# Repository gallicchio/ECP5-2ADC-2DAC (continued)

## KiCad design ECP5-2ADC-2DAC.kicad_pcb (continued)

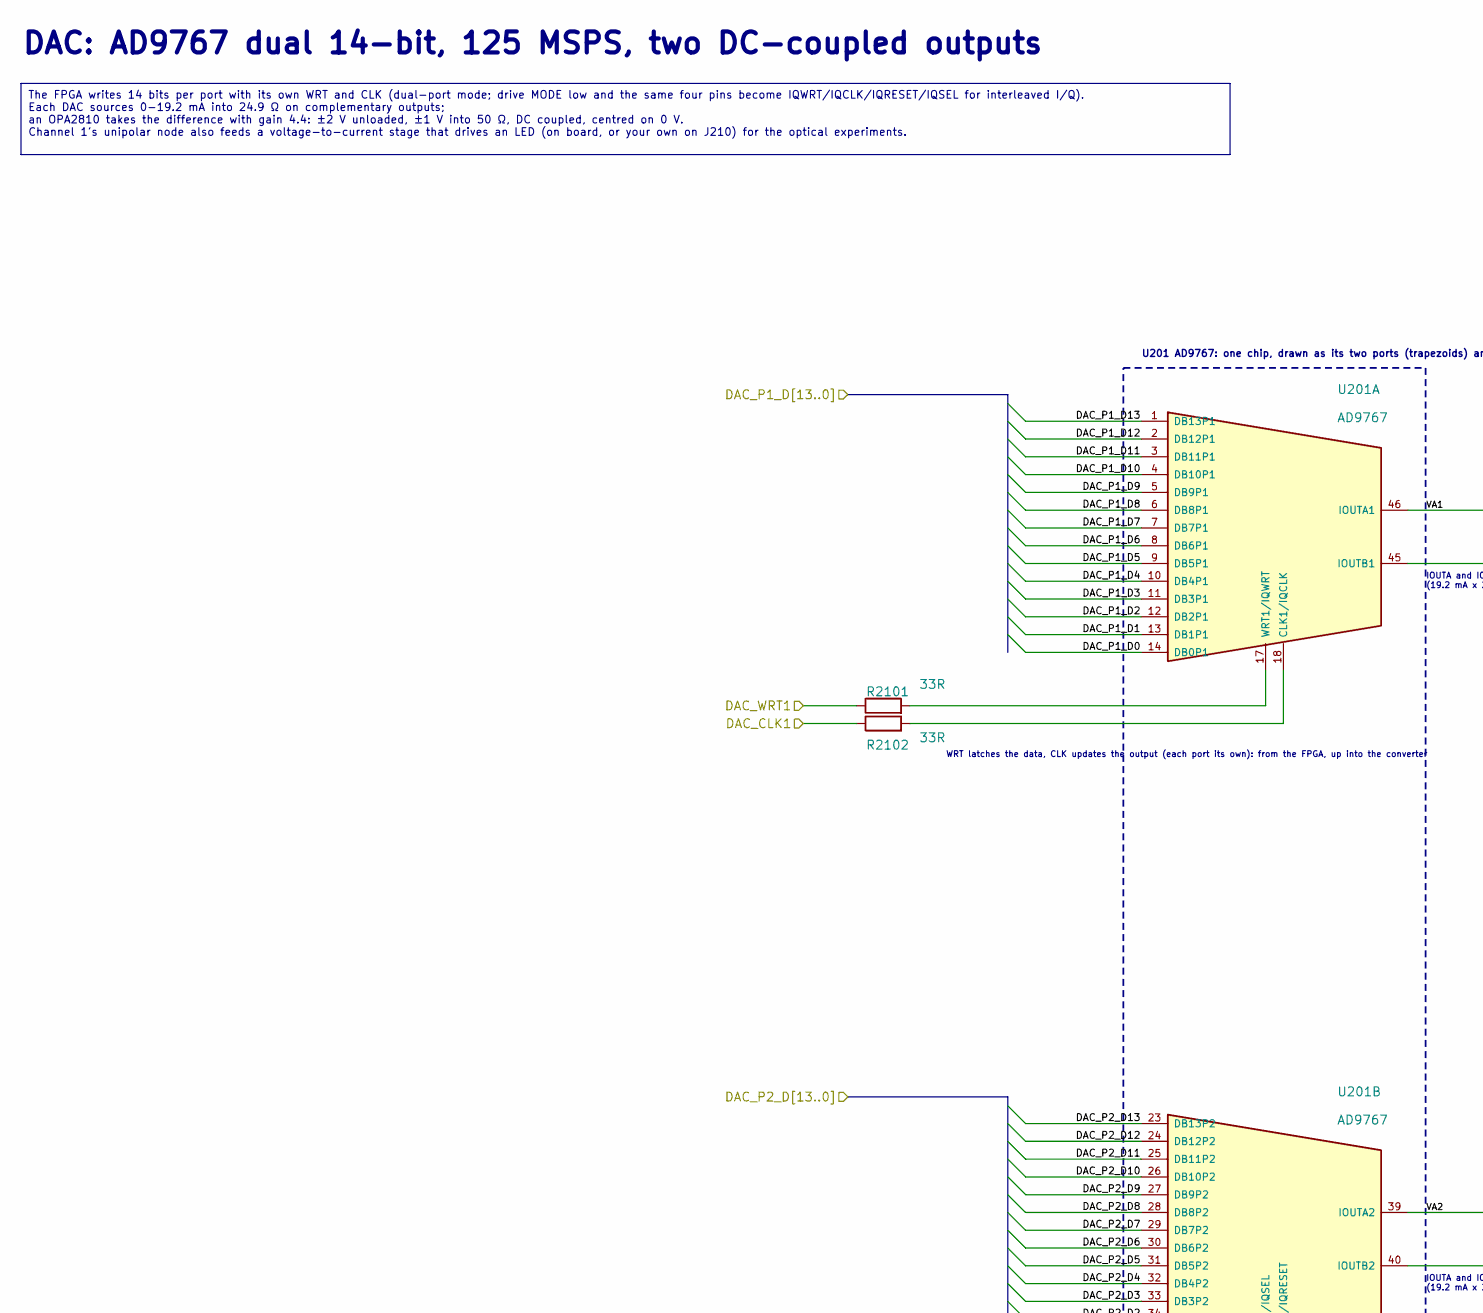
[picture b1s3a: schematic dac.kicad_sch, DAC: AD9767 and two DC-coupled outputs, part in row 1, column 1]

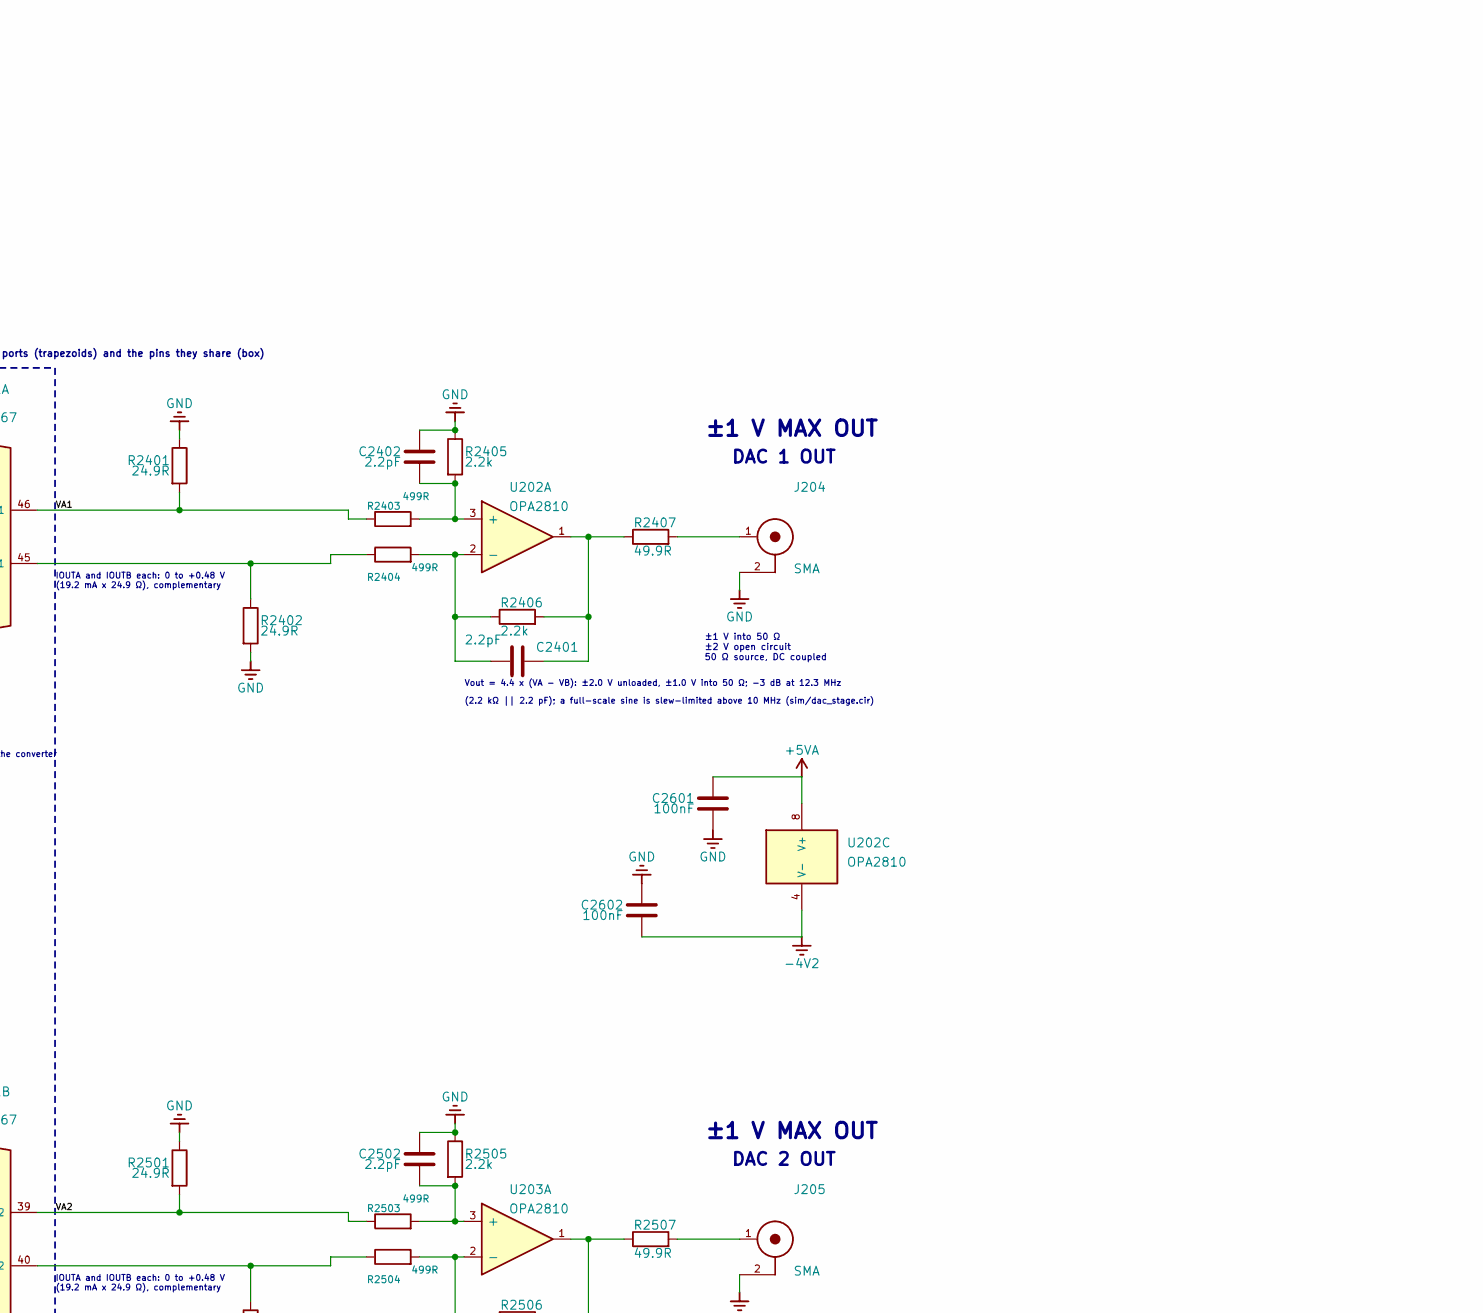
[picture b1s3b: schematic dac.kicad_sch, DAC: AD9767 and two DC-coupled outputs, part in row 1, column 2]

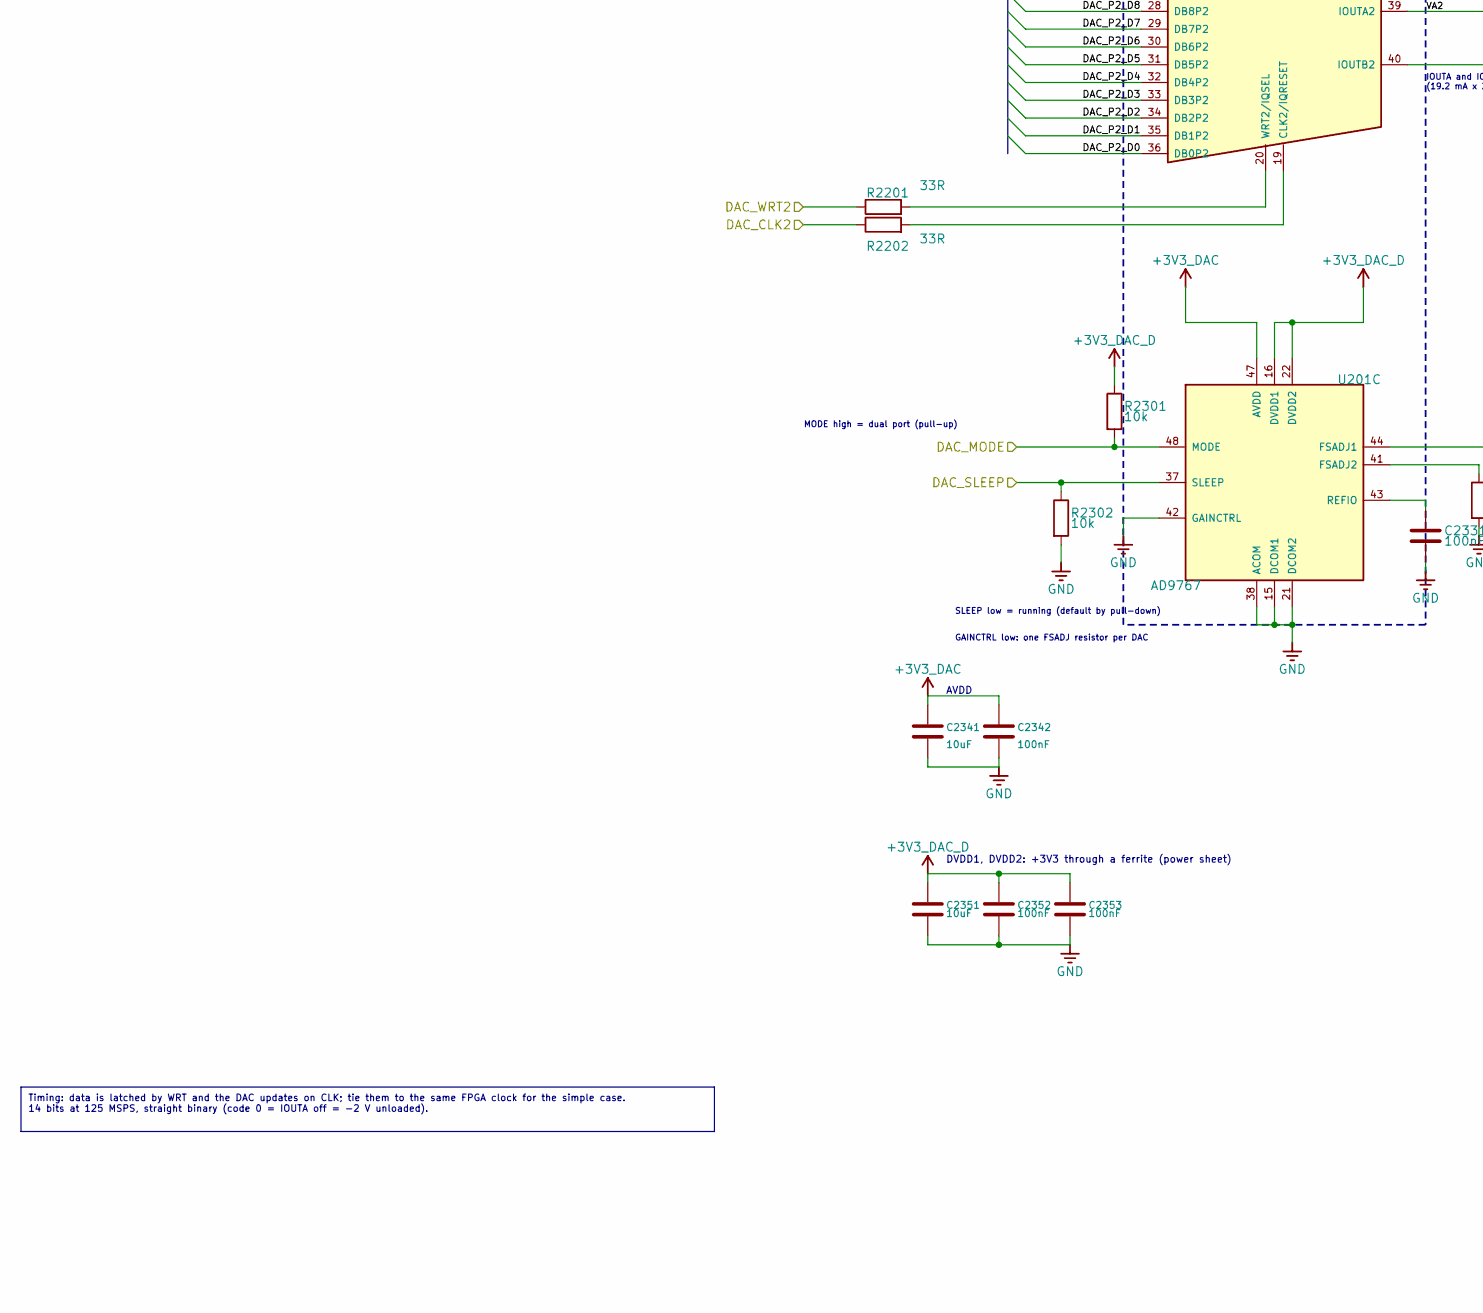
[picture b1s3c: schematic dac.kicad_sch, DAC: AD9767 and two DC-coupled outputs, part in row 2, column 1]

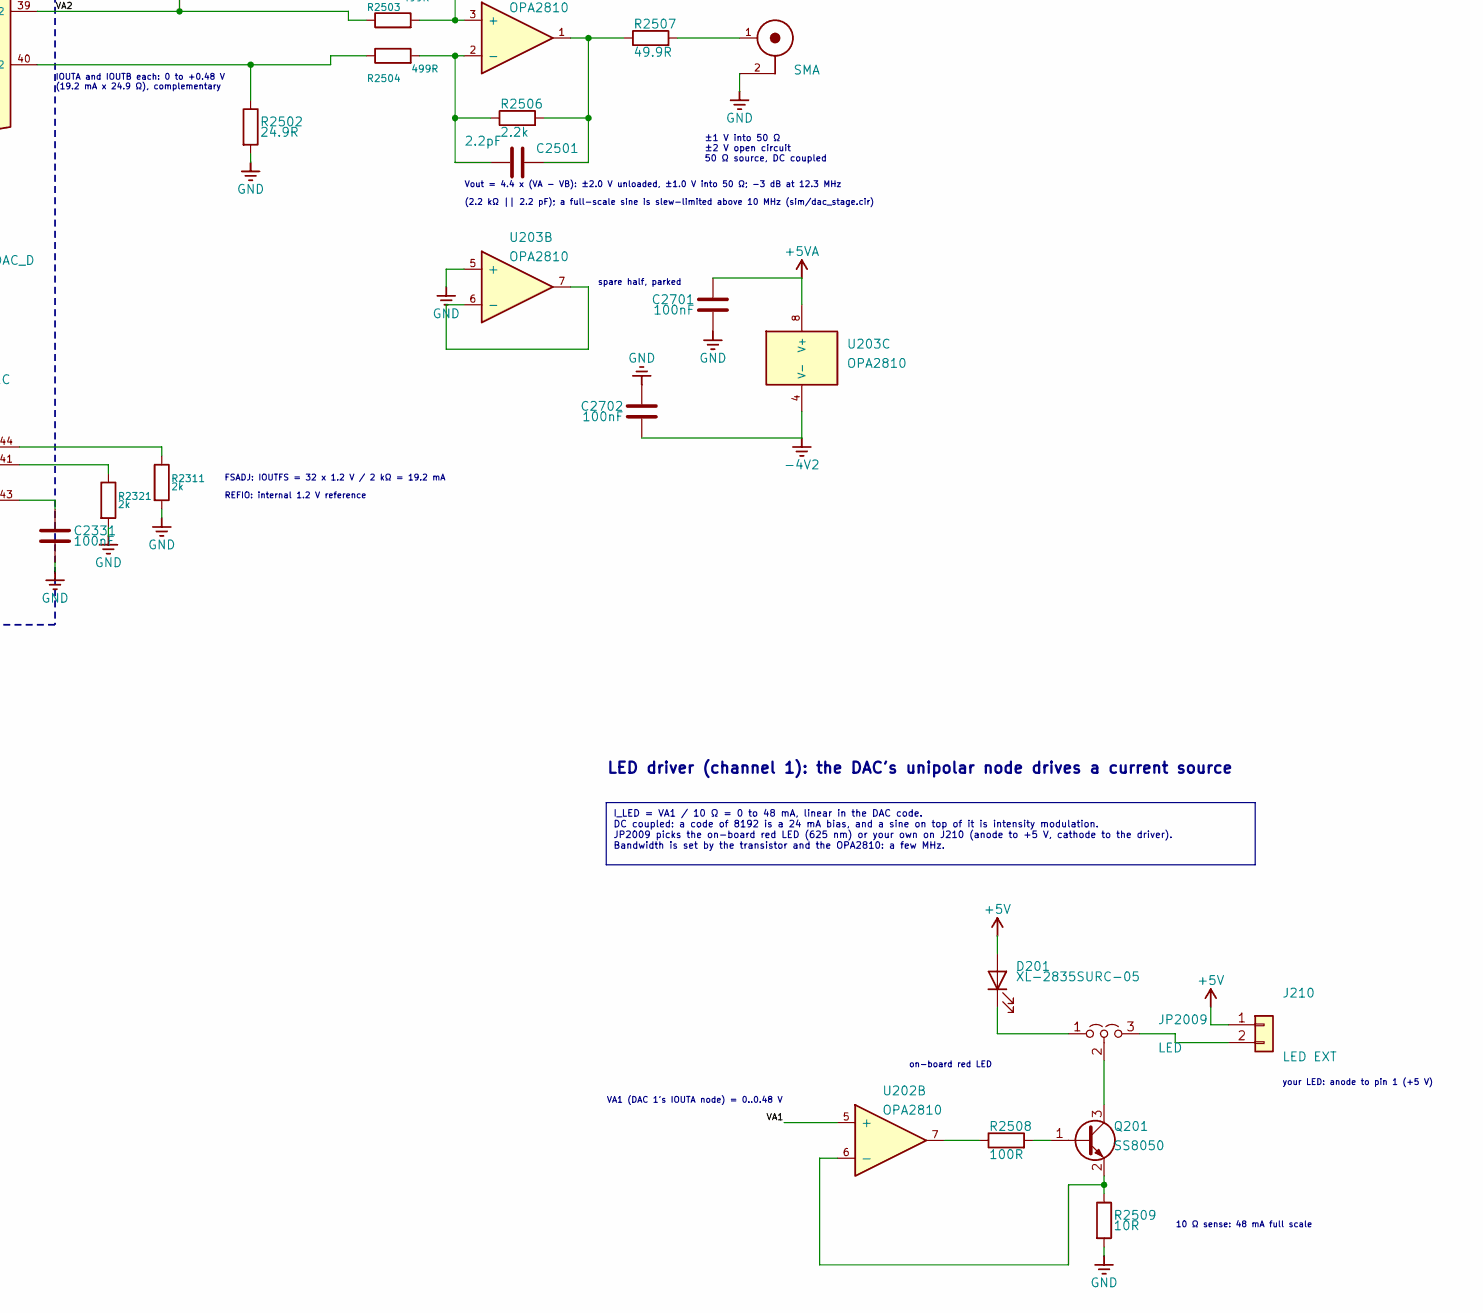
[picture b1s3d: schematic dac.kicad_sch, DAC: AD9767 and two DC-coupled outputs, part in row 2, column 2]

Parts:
C2331, C2342, C2352, C2353, C2601, C2602, C2701, C2702: 100nF; C_0402_1005Metric; LCSC C1525
C2341, C2351: 10uF; C_0603_1608Metric; LCSC C96446
C2401, C2402, C2501, C2502: 2.2pF; C_0402_1005Metric; LCSC C1559
D201: XL-2835SURC-05; LED-SMD_L3.5-W2.8-RD; LCSC C2843878
J204, J205: SMA; SMA_BAT_Wireless_BWSMA-KWE-Z001; LCSC C496551
J210: LED EXT; PinHeader_1x02_P2.54mm_Vertical; LCSC C492401
JP2009: LED; PinHeader_1x03_P2.54mm_Vertical; LCSC C2937625
Q201: SS8050; SOT-23; LCSC C2150
R2101, R2102, R2201, R2202: 33R; R_0603_1608Metric; LCSC C23140
R2301, R2302: 10k; R_0603_1608Metric; LCSC C25804
R2311, R2321: 2k; R_0603_1608Metric; LCSC C22975
R2401, R2402, R2501, R2502: 24.9R; R_0603_1608Metric; LCSC C22916
R2403, R2404, R2503, R2504: 499R; R_0603_1608Metric; LCSC C137714
R2405, R2406, R2505, R2506: 2.2k; R_0603_1608Metric; LCSC C4190
R2407, R2507: 49.9R; R_0603_1608Metric; LCSC C23185
R2508: 100R; R_0603_1608Metric; LCSC C22775
R2509: 10R; R_0603_1608Metric; LCSC C22859
U201: AD9767; LQFP-48_7x7mm_P0.5mm; LCSC C653820
U202, U203: OPA2810; SOIC-8_3.9x4.9mm_P1.27mm; LCSC C1849413

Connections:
+3V3_DAC: C2341.1, C2342.1, U201.47 (AVDD); also elsewhere on the board
+3V3_DAC_D: C2351.1, C2352.1, C2353.1, R2301.1, U201.16 (DVDD1), U201.22 (DVDD2); also elsewhere on the board
+5V: D201.2 (A), J210.1; also elsewhere on the board
+5VA: C2601.1, C2701.1, U202.8 (V+), U203.8 (V+); also elsewhere on the board
-4V2: C2602.2, C2702.2, U202.4 (V-), U203.4 (V-); also elsewhere on the board
/DAC/DAC_CLK1: R2102.1; also elsewhere on the board
/DAC/DAC_CLK2: R2202.1; also elsewhere on the board
/DAC/DAC_MODE: R2301.2, U201.48 (MODE); also elsewhere on the board
/DAC/DAC_P1_D0: U201.14 (DB0P1); also elsewhere on the board
/DAC/DAC_P1_D1: U201.13 (DB1P1); also elsewhere on the board
/DAC/DAC_P1_D2: U201.12 (DB2P1); also elsewhere on the board
/DAC/DAC_P1_D3: U201.11 (DB3P1); also elsewhere on the board
/DAC/DAC_P1_D4: U201.10 (DB4P1); also elsewhere on the board
/DAC/DAC_P1_D5: U201.9 (DB5P1); also elsewhere on the board
/DAC/DAC_P1_D6: U201.8 (DB6P1); also elsewhere on the board
/DAC/DAC_P1_D7: U201.7 (DB7P1); also elsewhere on the board
/DAC/DAC_P1_D8: U201.6 (DB8P1); also elsewhere on the board
/DAC/DAC_P1_D9: U201.5 (DB9P1); also elsewhere on the board
/DAC/DAC_P1_D10: U201.4 (DB10P1); also elsewhere on the board
/DAC/DAC_P1_D11: U201.3 (DB11P1); also elsewhere on the board
/DAC/DAC_P1_D12: U201.2 (DB12P1); also elsewhere on the board
/DAC/DAC_P1_D13: U201.1 (DB13P1); also elsewhere on the board
/DAC/DAC_P2_D0: U201.36 (DB0P2); also elsewhere on the board
/DAC/DAC_P2_D1: U201.35 (DB1P2); also elsewhere on the board
/DAC/DAC_P2_D2: U201.34 (DB2P2); also elsewhere on the board
/DAC/DAC_P2_D3: U201.33 (DB3P2); also elsewhere on the board
/DAC/DAC_P2_D4: U201.32 (DB4P2); also elsewhere on the board
/DAC/DAC_P2_D5: U201.31 (DB5P2); also elsewhere on the board
/DAC/DAC_P2_D6: U201.30 (DB6P2); also elsewhere on the board
/DAC/DAC_P2_D7: U201.29 (DB7P2); also elsewhere on the board
/DAC/DAC_P2_D8: U201.28 (DB8P2); also elsewhere on the board
/DAC/DAC_P2_D9: U201.27 (DB9P2); also elsewhere on the board
/DAC/DAC_P2_D10: U201.26 (DB10P2); also elsewhere on the board
/DAC/DAC_P2_D11: U201.25 (DB11P2); also elsewhere on the board
/DAC/DAC_P2_D12: U201.24 (DB12P2); also elsewhere on the board
/DAC/DAC_P2_D13: U201.23 (DB13P2); also elsewhere on the board
/DAC/DAC_SLEEP: R2302.1, U201.37 (SLEEP); also elsewhere on the board
/DAC/DAC_WRT1: R2101.1; also elsewhere on the board
/DAC/DAC_WRT2: R2201.1; also elsewhere on the board
/DAC/VA1: R2401.2, R2403.1, U201.46 (IOUTA1), U202.5 (+)
/DAC/VA2: R2501.2, R2503.1, U201.39 (IOUTA2)
GND: C2331.2, C2341.2, C2342.2, C2351.2, C2352.2, C2353.2, C2402.1, C2502.1, C2601.2, C2602.1, C2701.2, C2702.1, J204.2, J205.2, R2302.2, R2311.2, R2321.2, R2401.1, R2402.2, R2405.1, R2501.1, R2502.2, R2505.1, R2509.2, U201.15 (DCOM1), U201.21 (DCOM2), U201.38 (ACOM), U201.42 (GAINCTRL), U203.5 (+); also elsewhere on the board
unnamed: C2401.2, R2406.2, R2407.1, U202.1
unnamed: C2501.2, R2506.2, R2507.1, U203.1
unnamed: D201.1 (K), JP2009.1 (A)
unnamed: J204.1, R2407.2
unnamed: J205.1, R2507.2
unnamed: J210.2, JP2009.3 (B)
unnamed: JP2009.2 (C), Q201.3 (C)
unnamed: Q201.1 (B), R2508.2
unnamed: Q201.2 (E), R2509.1, U202.6 (-)
unnamed: R2508.1, U202.7
unnamed: R2102.2, U201.18 (CLK1/IQCLK)
unnamed: R2402.1, R2404.1, U201.45 (IOUTB1)
unnamed: R2101.2, U201.17 (WRT1/IQWRT)
unnamed: R2202.2, U201.19 (CLK2/IQRESET)
unnamed: R2502.1, R2504.1, U201.40 (IOUTB2)
unnamed: R2201.2, U201.20 (WRT2/IQSEL)
unnamed: R2311.1, U201.44 (FSADJ1)
unnamed: R2321.1, U201.41 (FSADJ2)
unnamed: C2331.1, U201.43 (REFIO)
unnamed: C2402.2, R2403.2, R2405.2, U202.3 (+)
unnamed: C2401.1, R2404.2, R2406.1, U202.2 (-)
unnamed: C2502.2, R2503.2, R2505.2, U203.3 (+)
unnamed: C2501.1, R2504.2, R2506.1, U203.2 (-)
unnamed: U203.6 (-), U203.7

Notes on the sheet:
DVDD1, DVDD2: +3V3 through a ferrite (power sheet)
WRT latches the data, CLK updates the output (each port its own): from the FPGA, up into the converter
on-board red LED
Vout = 4.4 x (VA - VB): ±2.0 V unloaded, ±1.0 V into 50 Ω; -3 dB at 12.3 MHz
REFIO: internal 1.2 V reference
LED driver (channel 1): the DAC's unipolar node drives a current source
VA1 (DAC 1's IOUTA node) = 0..0.48 V
SLEEP low = running (default by pull-down)
±1 V MAX OUT
DAC 1 OUT
U201 AD9767: one chip, drawn as its two ports (trapezoids) and the pins they share (box)
MODE high = dual port (pull-up)
(2.2 kΩ || 2.2 pF); a full-scale sine is slew-limited above 10 MHz (sim/dac_stage.cir)
IOUTA and IOUTB each: 0 to +0.48 V (19.2 mA x 24.9 Ω), complementary
±1 V into 50 Ω ±2 V open circuit 50 Ω source, DC coupled
spare half, parked
DAC 2 OUT
FSADJ: IOUTFS = 32 x 1.2 V / 2 kΩ = 19.2 mA
DAC: AD9767 dual 14-bit, 125 MSPS, two DC-coupled outputs
10 Ω sense: 48 mA full scale
GAINCTRL low: one FSADJ resistor per DAC
your LED: anode to pin 1 (+5 V)
AVDD
I_LED = VA1 / 10 Ω = 0 to 48 mA, linear in the DAC code. DC coupled: a code of 8192 is a 24 mA bias, and a sine on top of it is intensity modulation. JP2009 picks the on-board red LED (625 nm) or your own on J210 (anode to +5 V, cathode to the driver). Bandwidth is set by the transistor and the OPA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
Timing: data is latched by WRT and the DAC updates on CLK; tie them to the same FPGA clock for the simple case. 14 bits at 125 MSPS, straight binary (code 0 = IOUTA off = -2 V unloaded).
The FPGA writes 14 bits per port with its own WRT and CLK (dual-port mode; drive MODE low and the same four pins become IQWRT/IQCLK/IQRESET/IQSEL for interleaved I/Q). Each DAC sources 0-19.2 mA into 24.9 Ω on complementary outputs; an OPA2810 takes the difference with gain 4.4: ±2 V unloaded, ±1 V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

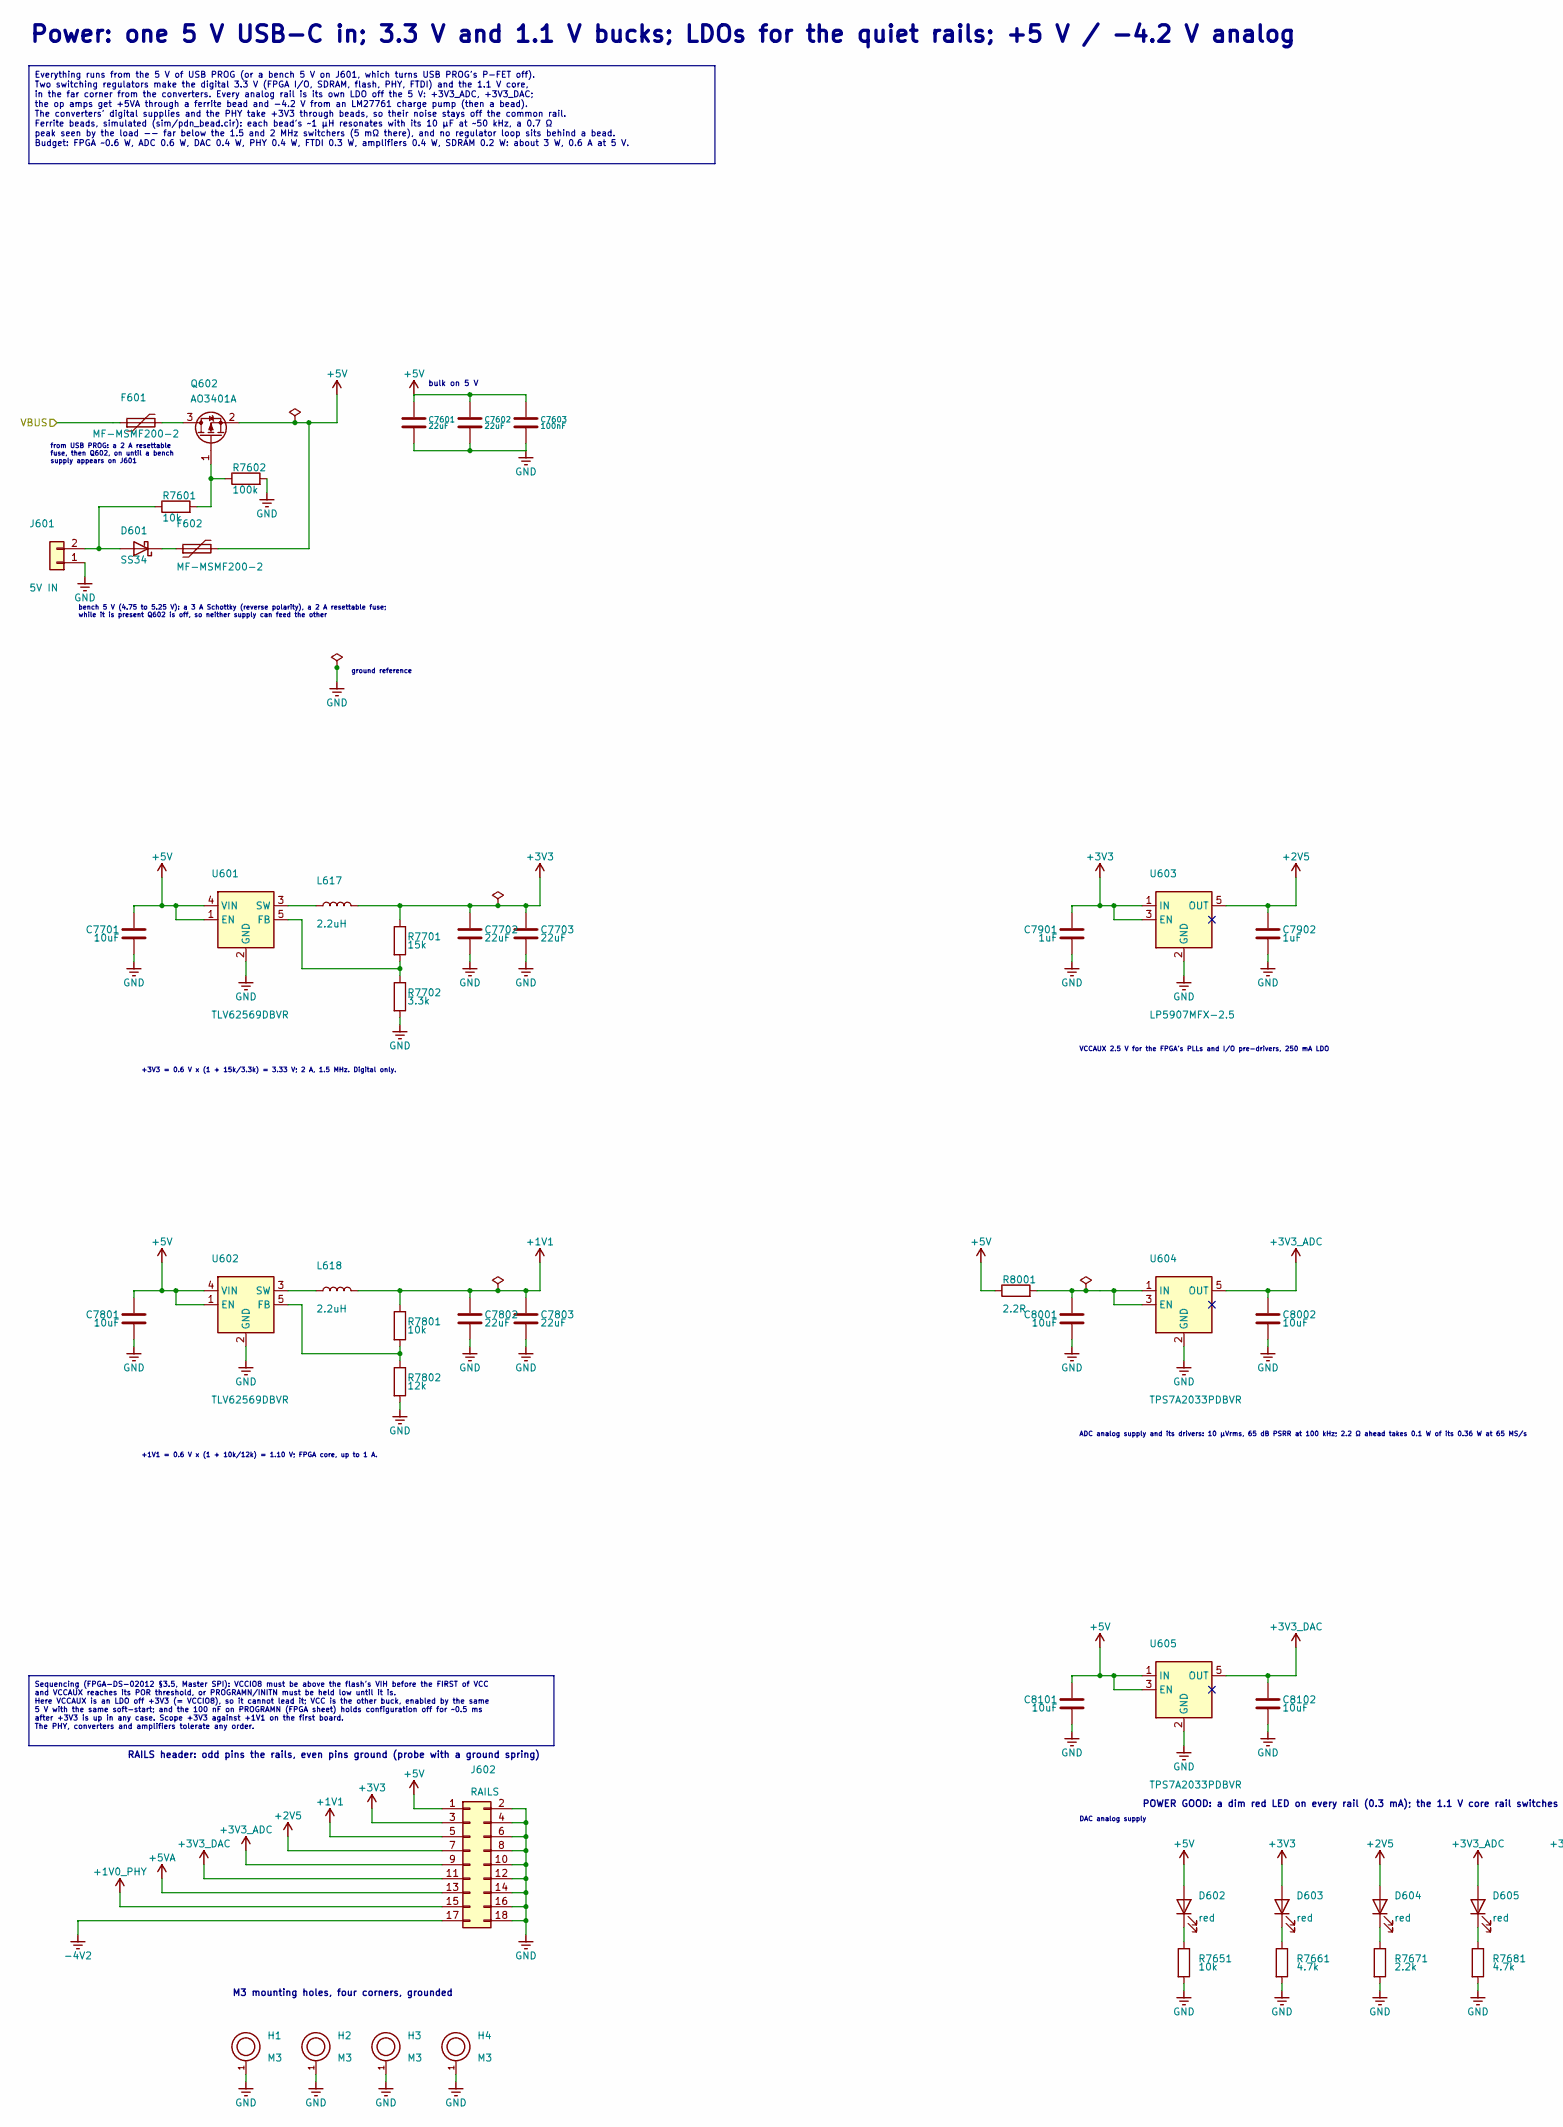
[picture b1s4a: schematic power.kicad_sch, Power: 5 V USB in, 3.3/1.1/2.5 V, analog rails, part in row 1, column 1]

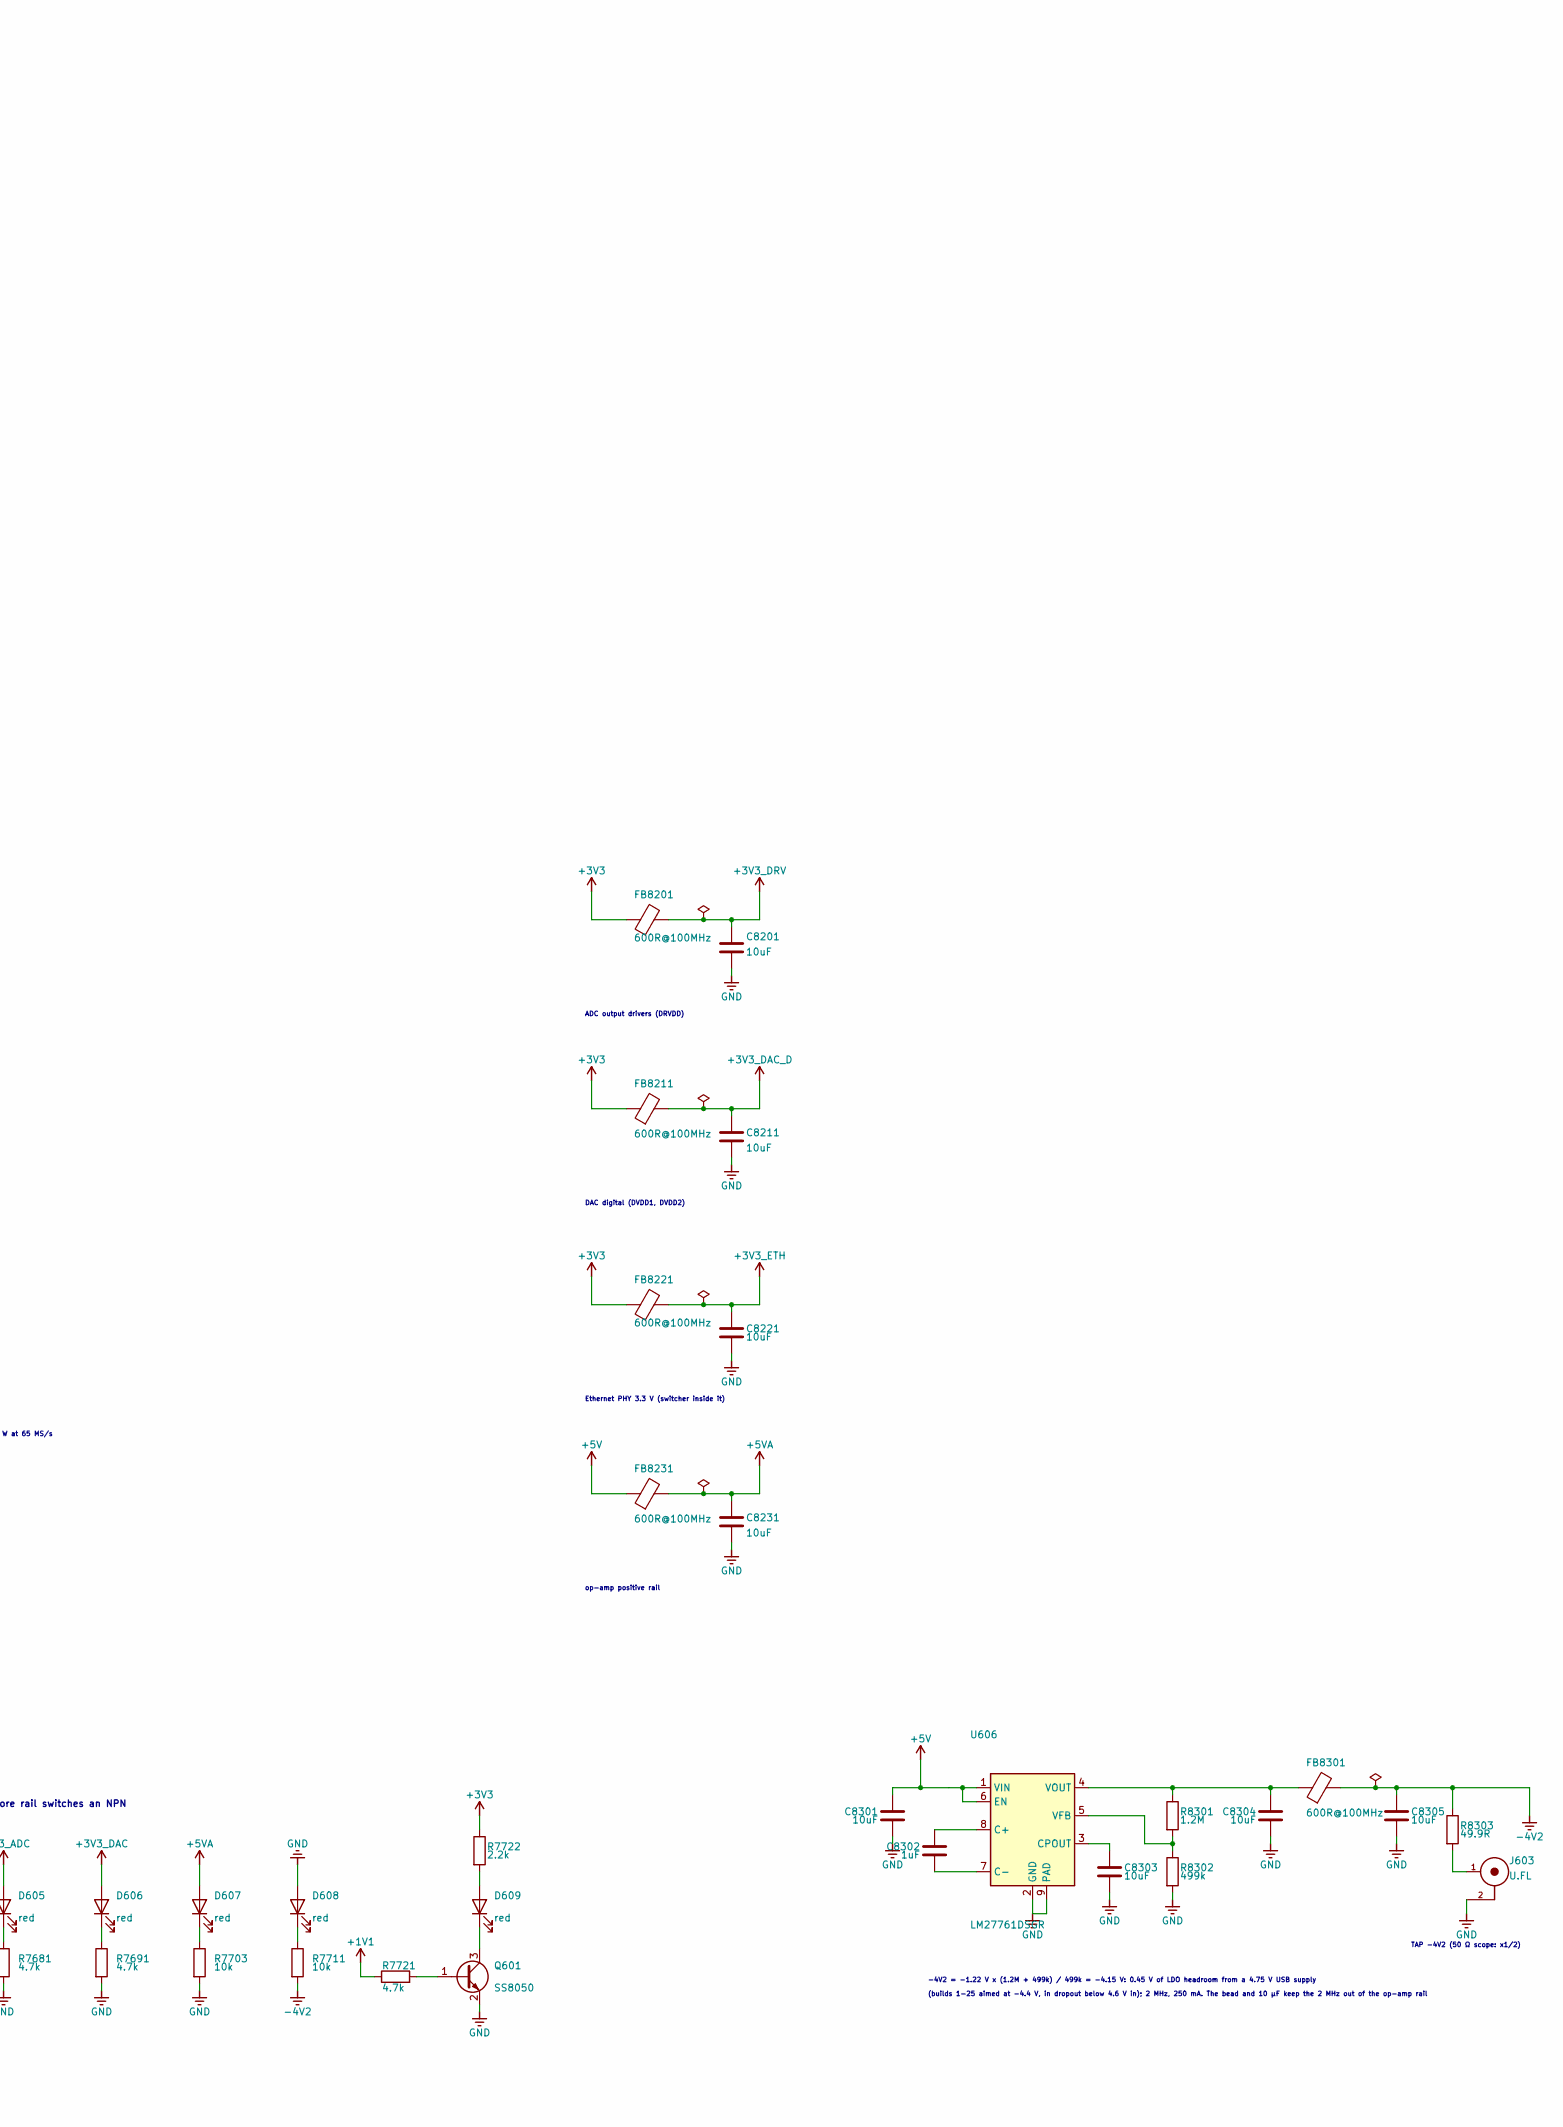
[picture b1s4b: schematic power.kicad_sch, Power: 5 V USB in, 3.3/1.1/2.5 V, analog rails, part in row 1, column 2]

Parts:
C7601, C7602, C7702, C7703, C7802, C7803: 22uF; C_0805_2012Metric; LCSC C45783
C7603: 100nF; C_0402_1005Metric; LCSC C1525
C7701, C7801, C8001, C8002, C8101, C8102, C8201, C8211, C8221, C8231, C8301, C8303, C8304, C8305: 10uF; C_0603_1608Metric; LCSC C96446
C7901, C7902, C8302: 1uF; C_0402_1005Metric; LCSC C52923
D601: SS34; D_SMA; LCSC C8678
D602, D603, D604, D605, D606, D607, D608, D609: red; LED_0603_1608Metric; LCSC C2286
F601, F602: MF-MSMF200-2; Fuse_1812_4532Metric; LCSC C210837
FB8201, FB8211, FB8221, FB8231, FB8301: 600R@100MHz; L_0603_1608Metric; LCSC C85833
H1, H2, H3, H4: M3; MountingHole_3.2mm_M3_Pad
J601: 5V IN; PinHeader_1x02_P2.54mm_Vertical; LCSC C492401
J602: RAILS; PinHeader_2x09_P2.54mm_Vertical; LCSC C492426
J603: U.FL; UFL_Hirose_U.FL-R-SMT-1; LCSC C88374
L617, L618: 2.2uH; IND-SMD_L4.0-W4.0; LCSC C279948
Q601: SS8050; SOT-23; LCSC C2150
Q602: AO3401A; SOT-23; LCSC C15127
R7601, R7651, R7703, R7711, R7801: 10k; R_0603_1608Metric; LCSC C25804
R7602: 100k; R_0603_1608Metric; LCSC C25803
R7661, R7681, R7691, R7721: 4.7k; R_0603_1608Metric; LCSC C23162
R7671, R7722: 2.2k; R_0603_1608Metric; LCSC C4190
R7701: 15k; R_0603_1608Metric; LCSC C22809
R7702: 3.3k; R_0603_1608Metric; LCSC C22978
R7802: 12k; R_0603_1608Metric; LCSC C22790
R8001: 2.2R; R_1206_3216Metric; LCSC C2907376
R8301: 1.2M; R_0603_1608Metric; LCSC C22766
R8302: 499k; R_0603_1608Metric; LCSC C26751
R8303: 49.9R; R_0603_1608Metric; LCSC C23185
U601, U602: TLV62569DBVR; SOT-23-5; LCSC C141836
U603: LP5907MFX-2.5; SOT-23-5; LCSC C165132
U604, U605: TPS7A2033PDBVR; SOT-23-5; LCSC C2862740
U606: LM27761DSGR; DFN-8-1EP_2x2mm_P0.5mm_EP0.9x1.6mm; LCSC C129351

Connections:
+1V0_PHY: J602.15; also elsewhere on the board
+1V1: C7802.1, C7803.1, J602.5, L618.2, R7721.1, R7801.1; also elsewhere on the board
+2V5: C7902.1, D604.2 (A), J602.7, U603.5 (OUT); also elsewhere on the board
+3V3: C7702.1, C7703.1, C7901.1, D603.2 (A), FB8201.1, FB8211.1, FB8221.1, J602.3, L617.2, R7701.1, R7722.1, U603.1 (IN), U603.3 (EN); also elsewhere on the board
+3V3_ADC: C8002.1, D605.2 (A), J602.9, U604.5 (OUT); also elsewhere on the board
+3V3_DAC: C8102.1, D606.2 (A), J602.11, U605.5 (OUT); also elsewhere on the board
+3V3_DAC_D: C8211.1, FB8211.2; also elsewhere on the board
+3V3_DRV: C8201.1, FB8201.2; also elsewhere on the board
+3V3_ETH: C8221.1, FB8221.2; also elsewhere on the board
+5V: C7601.1, C7602.1, C7603.1, C7701.1, C7801.1, C8101.1, C8301.1, D602.2 (A), F602.2, FB8231.1, J602.1, Q602.2 (S), R8001.1, U601.1 (EN), U601.4 (VIN), U602.1 (EN), U602.4 (VIN), U605.1 (IN), U605.3 (EN), U606.1 (VIN), U606.6 (EN); also elsewhere on the board
+5VA: C8231.1, D607.2 (A), FB8231.2, J602.13; also elsewhere on the board
-4V2: C8305.1, FB8301.2, J602.17, R7711.2, R8303.1; also elsewhere on the board
/Power/VBUS: F601.1; also elsewhere on the board
GND: C7601.2, C7602.2, C7603.2, C7701.2, C7702.2, C7703.2, C7801.2, C7802.2, C7803.2, C7901.2, C7902.2, C8001.2, C8002.2, C8101.2, C8102.2, C8201.2, C8211.2, C8221.2, C8231.2, C8301.2, C8303.2, C8304.2, C8305.2, D608.2 (A), H1.1, H2.1, H3.1, H4.1, J601.1, J602.2, J602.4, J602.6, J602.8, J602.10, J602.12, J602.14, J602.16, J602.18, J603.2, Q601.2 (E), R7602.2, R7651.2, R7661.2, R7671.2, R7681.2, R7691.2, R7702.2, R7703.2, R7802.2, R8302.2, U601.2 (GND), U602.2 (GND), U603.2 (GND), U604.2 (GND), U605.2 (GND), U606.2 (GND), U606.9 (PAD); also elsewhere on the board
unnamed: D601.2 (A), J601.2, R7601.1
unnamed: D601.1 (K), F602.1
unnamed: D602.1 (K), R7651.1
unnamed: D603.1 (K), R7661.1
unnamed: D604.1 (K), R7671.1
unnamed: D605.1 (K), R7681.1
unnamed: D606.1 (K), R7691.1
unnamed: D607.1 (K), R7703.1
unnamed: D608.1 (K), R7711.1
unnamed: D609.2 (A), R7722.2
unnamed: D609.1 (K), Q601.3 (C)
unnamed: J603.1, R8303.2
unnamed: Q601.1 (B), R7721.2
unnamed: F601.2, Q602.3 (D)
unnamed: Q602.1 (G), R7601.2, R7602.1
unnamed: R7701.2, R7702.1, U601.5 (FB)
unnamed: L617.1, U601.3 (SW)
unnamed: R7801.2, R7802.1, U602.5 (FB)
unnamed: L618.1, U602.3 (SW)
unnamed: C8001.1, R8001.2, U604.1 (IN), U604.3 (EN)
unnamed: C8302.1, U606.8 (C+)
unnamed: C8302.2, U606.7 (C-)
unnamed: C8303.1, U606.3 (CPOUT)
unnamed: R8301.2, R8302.1, U606.5 (VFB)
unnamed: C8304.1, FB8301.1, R8301.1, U606.4 (VOUT)

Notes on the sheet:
-4V2 = -1.22 V x (1.2M + 499k) / 499k = -4.15 V: 0.45 V of LDO headroom from a 4.75 V USB supply
(builds 1-25 aimed at -4.4 V, in dropout below 4.6 V in); 2 MHz, 250 mA. The bead and 10 µF keep the 2 MHz out of the op-amp rail
bench 5 V (4.75 to 5.25 V): a 3 A Schottky (reverse polarity), a 2 A resettable fuse; while it is present Q602 is off, so neither supply can feed the other
bulk on 5 V
ground reference
RAILS header: odd pins the rails, even pins ground (probe with a ground spring)
M3 mounting holes, four corners, grounded
from USB PROG: a 2 A resettable fuse, then Q602, on until a bench supply appears on J601
Power: one 5 V USB-C in; 3.3 V and 1.1 V bucks; LDOs for the quiet rails; +5 V / -4.2 V analog
DAC analog supply
ADC analog supply and its drivers: 10 µVrms, 65 dB PSRR at 100 kHz; 2.2 Ω ahead takes 0.1 W of its 0.36 W at 65 MS/s
+1V1 = 0.6 V x (1 + 10k/12k) = 1.10 V; FPGA core, up to 1 A.
Ethernet PHY 3.3 V (switcher inside it)
VCCAUX 2.5 V for the FPGA's PLLs and I/O pre-drivers, 250 mA LDO
+3V3 = 0.6 V x (1 + 15k/3.3k) = 3.33 V; 2 A, 1.5 MHz. Digital only.
POWER GOOD: a dim red LED on every rail (0.3 mA); the 1.1 V core rail switches an NPN
DAC digital (DVDD1, DVDD2)
op-amp positive rail
TAP -4V2 (50 Ω scope: x1/2)
ADC output drivers (DRVDD)
Sequencing (FPGA-DS-02012 §3.5, Master SPI): VCCIO8 must be above the flash's VIH before the FIRST of VCC and VCCAUX reaches its POR threshold, or PROGRAMN/INITN must be held low until it is. Here VCCAUX is an LDO off +3V3 (= VCCIO8), so it cannot lead it; VCC is the other buck, enabled by the same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
Everything runs from the 5 V of USB PROG (or a bench 5 V on J601, which turns USB PROG's P-FET off). Two switching regulators make the digital 3.3 V (FPGA I/O, SDRAM, flash, PHY, FTDI) and the 1.1 V core, in the far corner from the converters. Every analog rail is its own LDO off the 5 V: +3V3_ADC,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
